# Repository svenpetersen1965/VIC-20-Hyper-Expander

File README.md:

# VIC-20-Hyper-Expander
The Hyper Expander is a cartridge for the Commodore VIC-20, which provides up to 16kB EPROM and up to 37kB RAM. It is a super-set of the original Commodore VIC-1211A Super Expander, which provides only 3k of RAM.

The Hyper Expander can hold up to two 27C512 EPROMs, the 8k memory bank of both EPROMs (A13...A15) can be selected for both EPROMs. The same selection applies to both of them. Each EPROM (IC1 and IC2) can be jumpered to two chip selects. That is BLK2 or BLK5 for IC1 and BLK1 or BLK3 for IC2. 

The RAM od two 32kB 62256 type static RAMs. The memory is divided into seven banks. Two 74LS148s decodes the active chip selects to one of each memory bank. The used chip selects can be configured with JP5 and JP4.

The BOM values do not include a case
* The calculated BOM value of Rev. 0 is: 12.86€ (12.12.2020)
* The calculated BOM value of Rev. 1 is: 15.23€ (11.04.2021)
* The calculated BOM value of Rev. 2 is: 16.17€ (02.11.2021)

# RAM issues
I was recently reported (May 2022), that there were cross-link issues with the Alliance 45ns and 55ns RAMs. I believe, that those might be too fast and that it is not an issue of the brand. Replacing those RAMs with slower models (70ns) has solved this problem. A friend has successfully used 100ns and 120ns RAMs as well (he had built a couple of the Hyper Expander). I am mainly using 70ns and 80ns RAMs and never found any issues with them. At least, my test software can recognize those problems.

# Testsoftware
Find the Testsoftware here: https://github.com/svenpetersen1965/VIC-20-RAM-Expansion-Test-Software

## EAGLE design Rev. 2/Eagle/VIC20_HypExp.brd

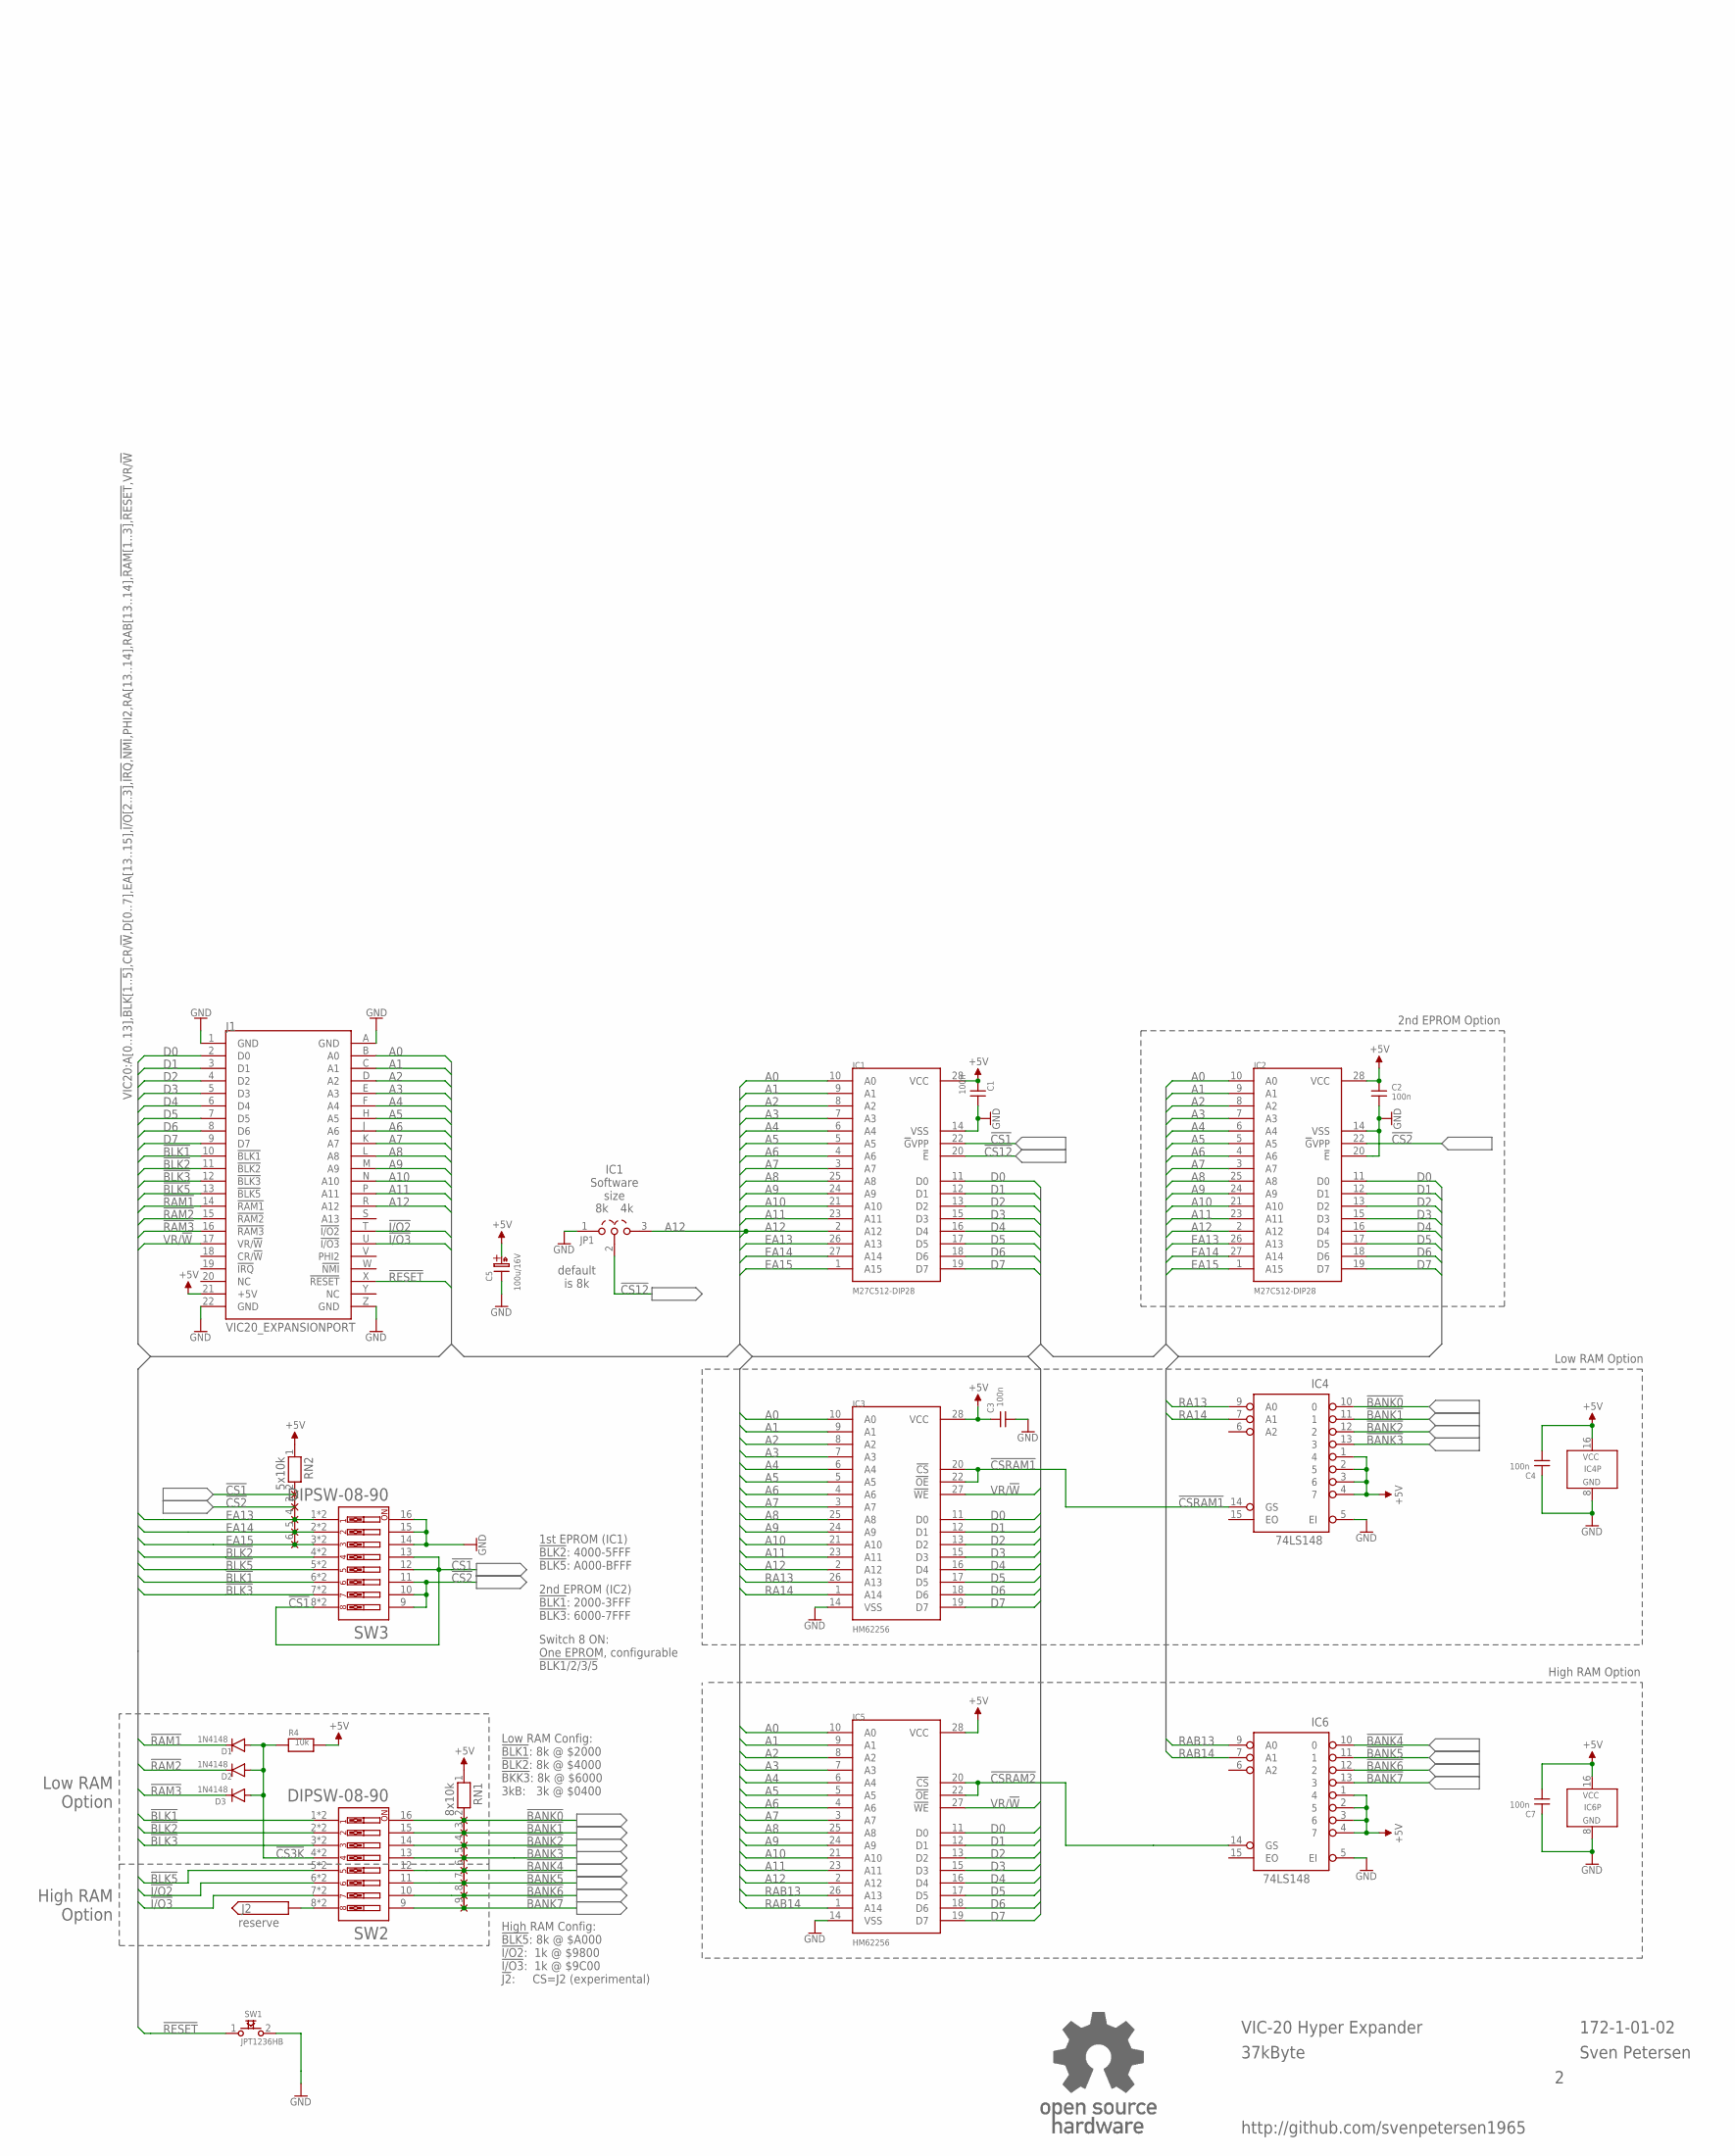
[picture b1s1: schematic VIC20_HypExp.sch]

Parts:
C1, C2, C3, C4, C7: 100n; C-2,5
C5: 100u/16V; C07/2,5
D1, D2, D3: 1N4148; DO-35/3
IC1, IC2: M27C512-DIP28; DIL28-6
IC3, IC5: HM62256; DIL28-6
IC4, IC6: 74LS148; DIL-16
J1: VIC20_EXPANSIONPORT; VIC20_EXPANSION
J2: PINHD-1X1; 1X01
JP1: COMBI-3P
R4: 10k; R-10
RN1: 8x10k; RN-9
RN2: 5x10k; RN-6
SW1: JPT1236HB; JTP_1236HB
SW2, SW3: DIPSW-08-90
U$2: OPEN_SOURCE_HW; OPENHW

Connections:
!BANK0: IC4.10 (0), RN1.2, SW2.16
!BANK1: IC4.11 (1), RN1.3, SW2.15
!BANK2: IC4.12 (2), RN1.4, SW2.14
!BANK3: IC4.13 (3), RN1.5, SW2.13
!BANK4: IC6.10 (0), RN1.6, SW2.12
!BANK5: IC6.11 (1), RN1.7, SW2.11
!BANK6: IC6.12 (2), RN1.8, SW2.10
!BANK7: IC6.13 (3), RN1.9, SW2.9
!BLK1: J1.10 (!BLK1), SW2.1, SW2.1A (1), SW3.6, SW3.6A (6)
!BLK2: J1.11 (!BLK2), SW2.2, SW2.2A (2), SW3.4, SW3.4A (4)
!BLK3: J1.12 (!BLK3), SW2.3, SW2.3A (3), SW3.7, SW3.7A (7)
!BLK5: J1.13 (!BLK5), SW2.5, SW2.5A (5), SW3.5, SW3.5A (5)
!CS1: IC1.22 (!G!VPP), RN2.2, SW3.8, SW3.8A (8), SW3.12, SW3.13
!CS2: IC2.22 (!G!VPP), RN2.3, SW3.9, SW3.10, SW3.11
!CS3K: D1.A, D2.A, D3.A, R4.1, SW2.4, SW2.4A (4)
!CS12: IC1.20 (!E), JP1.2
!CSRAM1: IC3.20 (!CS), IC3.22 (!OE), IC4.14 (GS)
!CSRAM2: IC5.20 (!CS), IC5.22 (!OE), IC6.14 (GS)
!I/O2: J1.T (!I/O2), SW2.6, SW2.6A (6)
!I/O3: J1.U (!I/O3), SW2.7, SW2.7A (7)
!RAM1: D1.K, J1.14 (!RAM1)
!RAM2: D2.K, J1.15 (!RAM2)
!RAM3: D3.K, J1.16 (!RAM3)
!RESET: J1.X (!RESET), SW1.1
+5V: C1.1, C2.1, C3.2, C4.1, C5.A (+), C7.1, IC1.28 (VCC), IC2.28 (VCC), IC3.28 (VCC), IC4.1 (4), IC4.2 (5), IC4.3 (6), IC4.4 (7), IC4.16 (VCC), IC5.28 (VCC), IC6.1 (4), IC6.2 (5), IC6.3 (6), IC6.4 (7), IC6.16 (VCC), J1.21 (+5V), R4.2, RN1.1, RN2.1
A0: IC1.10 (A0), IC2.10 (A0), IC3.10 (A0), IC5.10 (A0), J1.B (A0)
A1: IC1.9 (A1), IC2.9 (A1), IC3.9 (A1), IC5.9 (A1), J1.C (A1)
A2: IC1.8 (A2), IC2.8 (A2), IC3.8 (A2), IC5.8 (A2), J1.D (A2)
A3: IC1.7 (A3), IC2.7 (A3), IC3.7 (A3), IC5.7 (A3), J1.E (A3)
A4: IC1.6 (A4), IC2.6 (A4), IC3.6 (A4), IC5.6 (A4), J1.F (A4)
A5: IC1.5 (A5), IC2.5 (A5), IC3.5 (A5), IC5.5 (A5), J1.H (A5)
A6: IC1.4 (A6), IC2.4 (A6), IC3.4 (A6), IC5.4 (A6), J1.J (A6)
A7: IC1.3 (A7), IC2.3 (A7), IC3.3 (A7), IC5.3 (A7), J1.K (A7)
A8: IC1.25 (A8), IC2.25 (A8), IC3.25 (A8), IC5.25 (A8), J1.L (A8)
A9: IC1.24 (A9), IC2.24 (A9), IC3.24 (A9), IC5.24 (A9), J1.M (A9)
A10: IC1.21 (A10), IC2.21 (A10), IC3.21 (A10), IC5.21 (A10), J1.N (A10)
A11: IC1.23 (A11), IC2.23 (A11), IC3.23 (A11), IC5.23 (A11), J1.P (A11)
A12: IC1.2 (A12), IC2.2 (A12), IC3.2 (A12), IC5.2 (A12), J1.R (A12), JP1.3
D0: IC1.11 (D0), IC2.11 (D0), IC3.11 (D0), IC5.11 (D0), J1.2 (D0)
D1: IC1.12 (D1), IC2.12 (D1), IC3.12 (D1), IC5.12 (D1), J1.3 (D1)
D2: IC1.13 (D2), IC2.13 (D2), IC3.13 (D2), IC5.13 (D2), J1.4 (D2)
D3: IC1.15 (D3), IC2.15 (D3), IC3.15 (D3), IC5.15 (D3), J1.5 (D3)
D4: IC1.16 (D4), IC2.16 (D4), IC3.16 (D4), IC5.16 (D4), J1.6 (D4)
D5: IC1.17 (D5), IC2.17 (D5), IC3.17 (D5), IC5.17 (D5), J1.7 (D5)
D6: IC1.18 (D6), IC2.18 (D6), IC3.18 (D6), IC5.18 (D6), J1.8 (D6)
D7: IC1.19 (D7), IC2.19 (D7), IC3.19 (D7), IC5.19 (D7), J1.9 (D7)
EA13: IC1.26 (A13), IC2.26 (A13), RN2.4, SW3.1, SW3.1A (1)
EA14: IC1.27 (A14), IC2.27 (A14), RN2.5, SW3.2, SW3.2A (2)
EA15: IC1.1 (A15), IC2.1 (A15), RN2.6, SW3.3, SW3.3A (3)
GND: C1.2, C2.2, C3.1, C4.2, C5.K (-), C7.2, IC1.14 (VSS), IC2.14 (VSS), IC2.20 (!E), IC3.14 (VSS), IC4.5 (EI), IC4.8 (GND), IC5.14 (VSS), IC6.5 (EI), IC6.8 (GND), J1.1 (GND), J1.22 (GND), J1.A (GND), J1.Z (GND), JP1.1, SW1.2, SW3.14, SW3.15, SW3.16
unnamed: J2.1, SW2.8, SW2.8A (8)
NC: J1.20 (NC)
RA13: IC3.26 (A13), IC4.9 (A0)
RA14: IC3.1 (A14), IC4.7 (A1)
RAB13: IC5.26 (A13), IC6.9 (A0)
RAB14: IC5.1 (A14), IC6.7 (A1)
VR/!W: IC3.27 (!WE), IC5.27 (!WE), J1.17 (VR/!W)

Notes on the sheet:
VIC-20 Hyper Expander
172-1-01-02
Sven Petersen
http://github.com/svenpetersen1965
reserve
37kByte
High RAM Option
Low RAM Option
Low RAM Option
2nd EPROM Option
1st EPROM (IC1) !BLK2!: 4000-5FFF !BLK5!: A000-BFFF
2nd EPROM (IC2) !BLK1!: 2000-3FFF !BLK3!: 6000-7FFF
Low RAM Config: !BLK1!: 8k @ $2000 !BLK2!: 8k @ $4000 !BKK3!: 8k @ $6000 3kB: 3k @ $0400
High RAM Config: !BLK5!: 8k @ $A000 !I/O2!: 1k @ $9800 !I/O3!: 1k @ $9C00 !J2!: CS=J2 (experimental)
Switch 8 ON: One EPROM, configurable !BLK1/2/3/5
IC1 Software size
default is 8k
High RAM Option

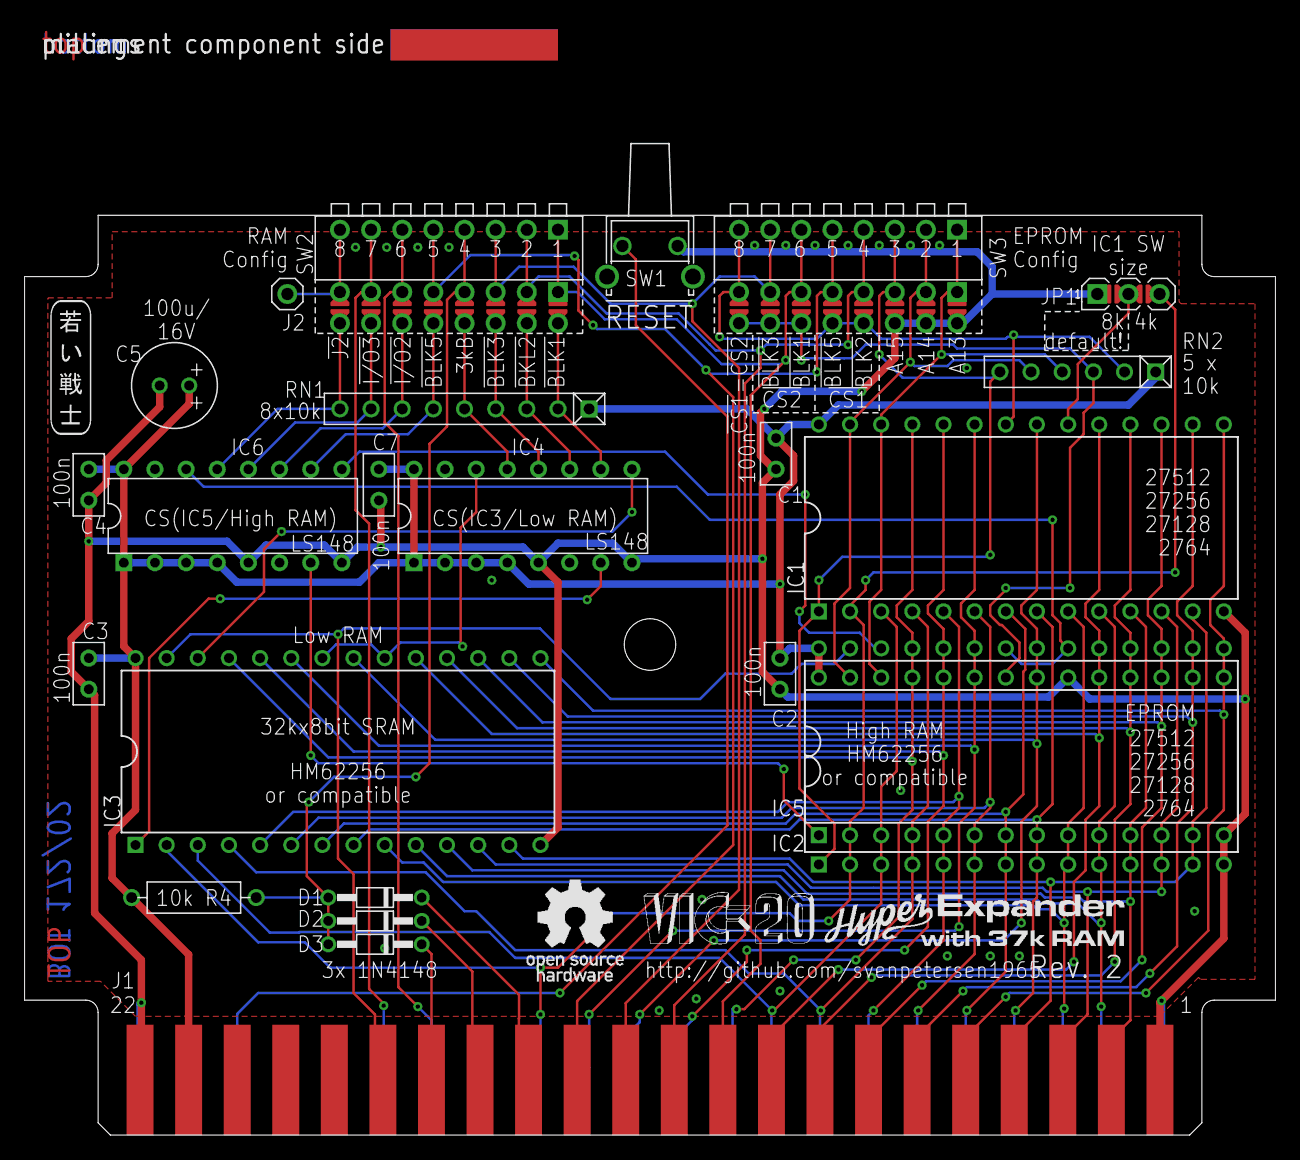
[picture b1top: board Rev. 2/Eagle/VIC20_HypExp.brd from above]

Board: 2 copper layers, 102.0 x 90.6 mm, 30 parts (0 on the bottom side), 56 nets.

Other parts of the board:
U$15: SVEN_TAG
U$16: 2LAYER
U$40: PCB-TITLE/
U$42: VIC-20
U$58: HYPER_EXPANDER

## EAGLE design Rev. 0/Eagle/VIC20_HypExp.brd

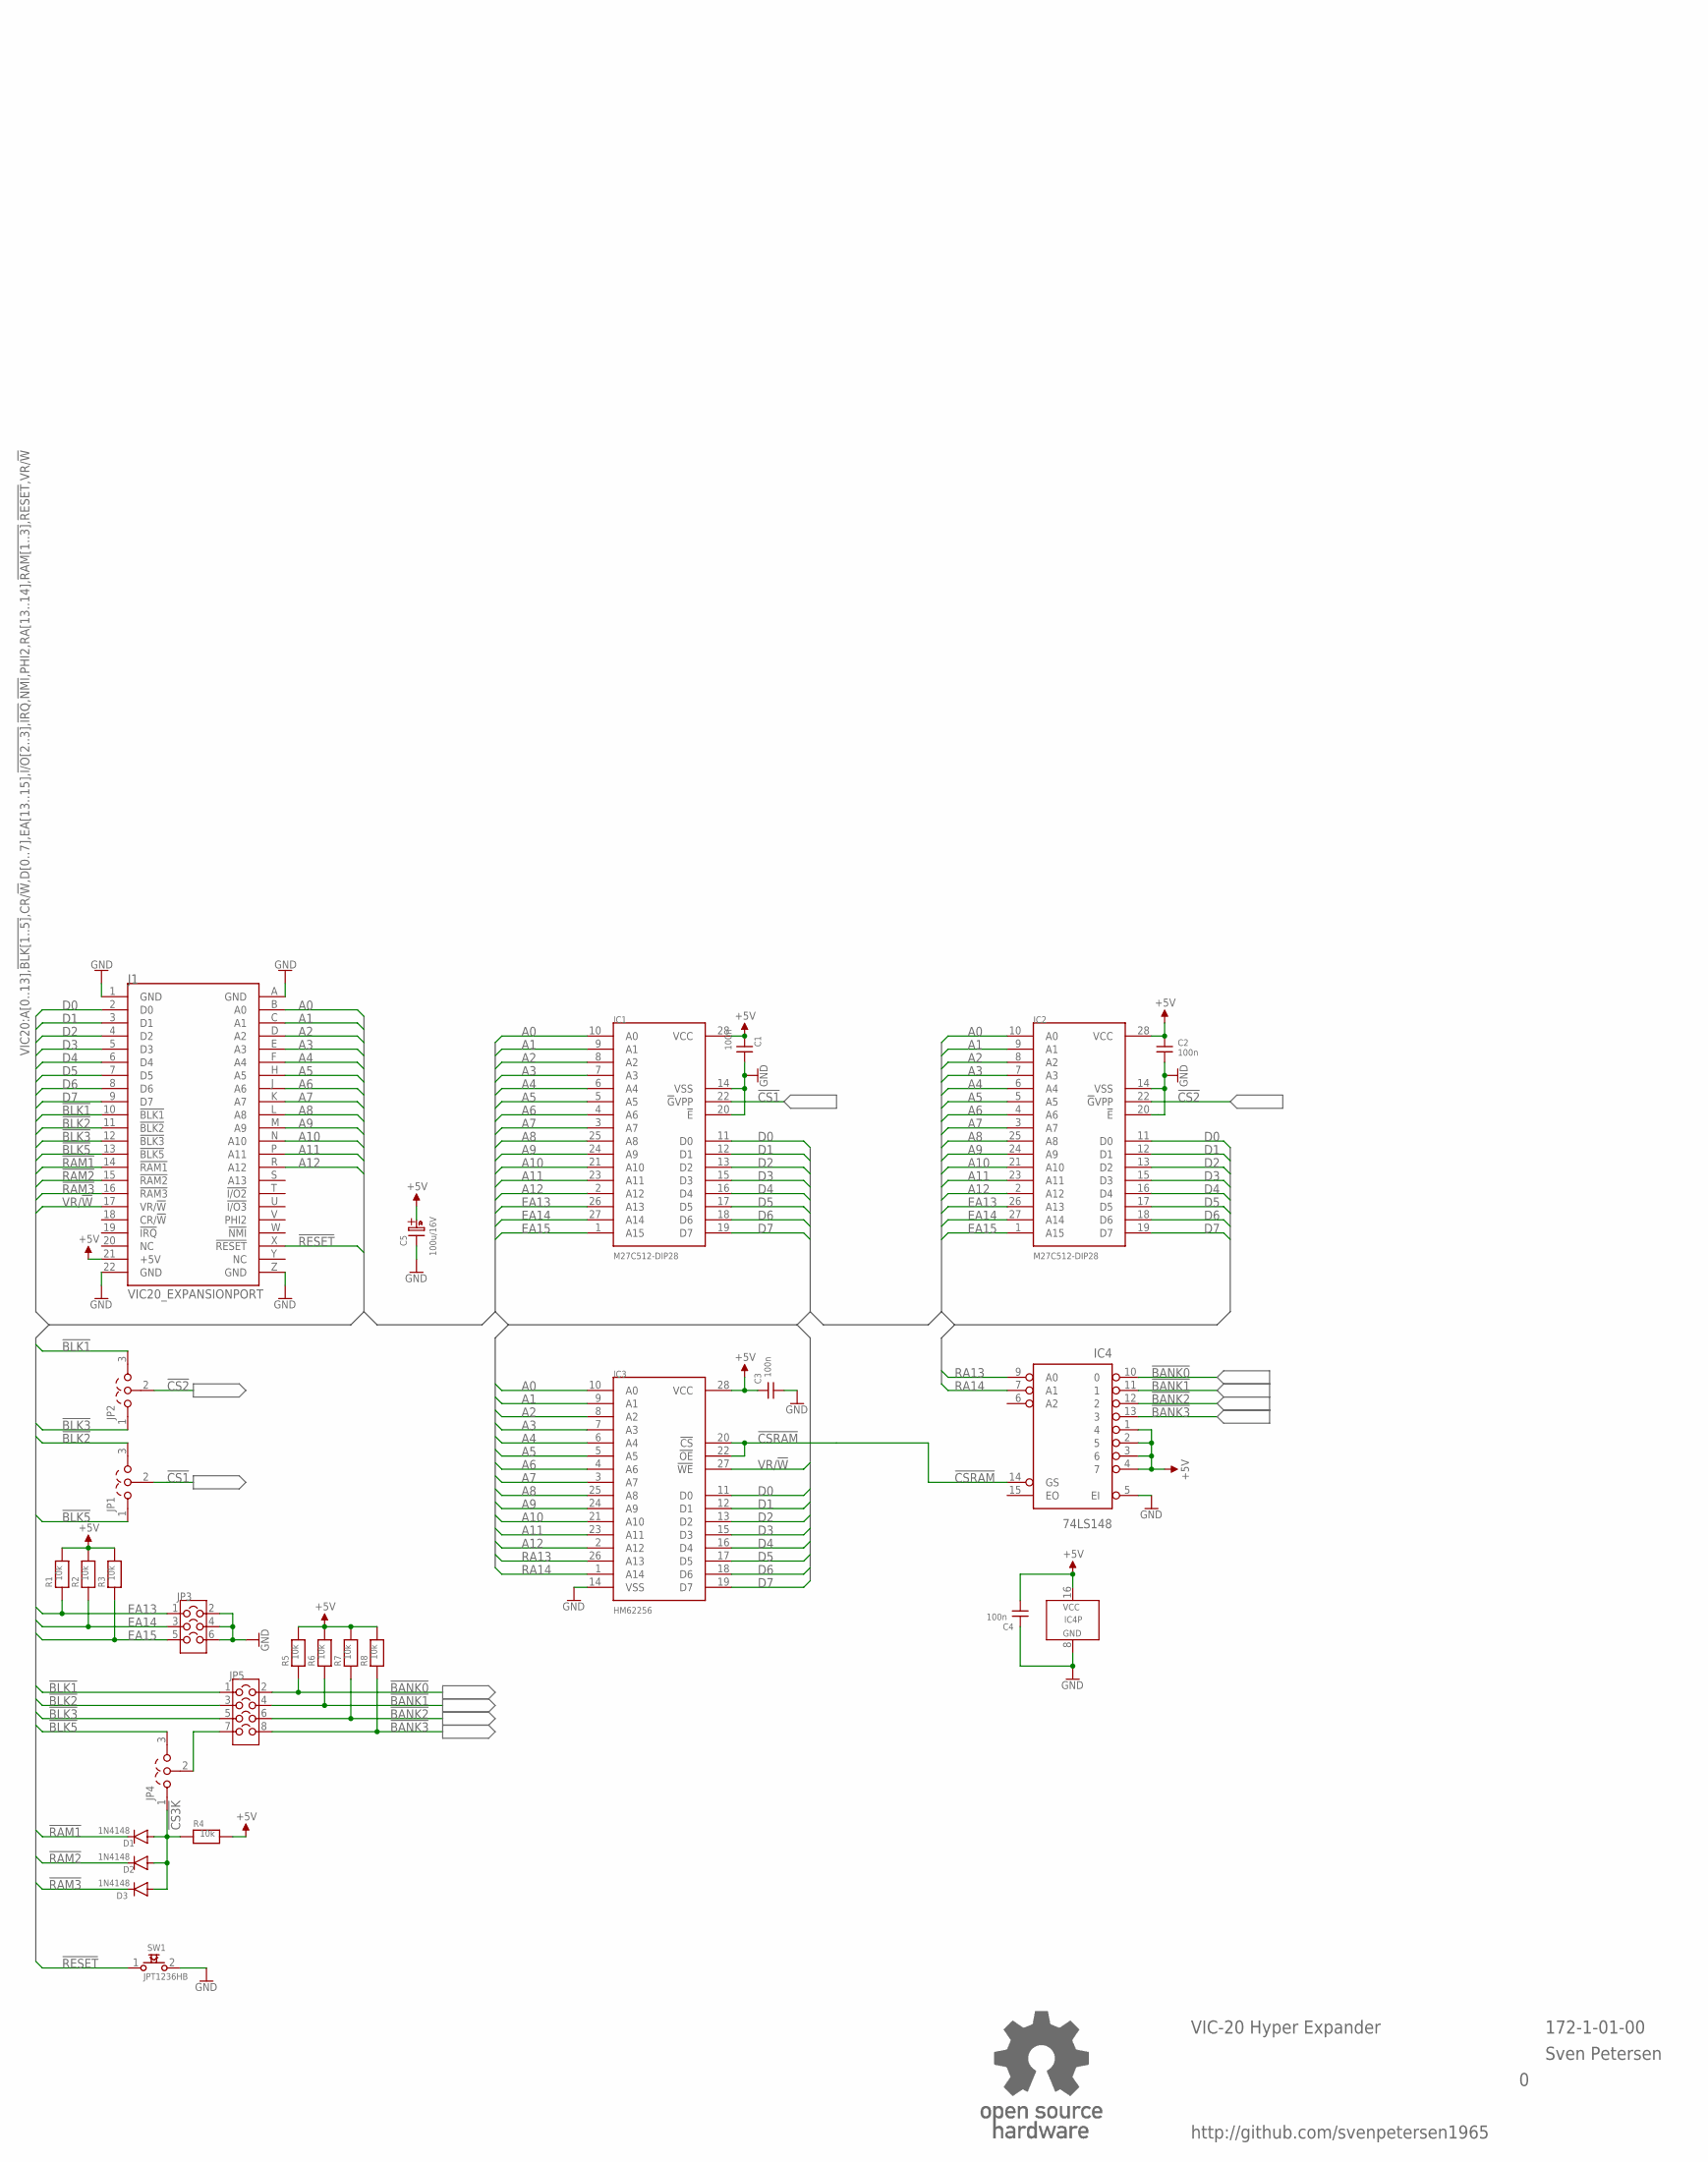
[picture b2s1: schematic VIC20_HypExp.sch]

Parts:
C1, C2, C3, C4: 100n; C-2,5
C5: 100u/16V; C07/2,5
D1, D2, D3: 1N4148; DO-35/3
IC1, IC2: M27C512-DIP28; DIL28-6
IC3: HM62256; DIL28-6
IC4: 74LS148; DIL-16
J1: VIC20_EXPANSIONPORT; VIC20_EXPANSION
JP1, JP2, JP4: COMBI-3P
JP3: COMBI-3X2P; COMBI-3X2
JP5: COMBI-4X2P; COMBI-4X2
R1, R2, R3, R4, R5, R6, R7, R8: 10k; R-10
SW1: JPT1236HB; JTP_1236HB
U$2: OPEN_SOURCE_HW; OPENHW

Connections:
!BANK0: IC4.10 (0), JP5.2, R5.1
!BANK1: IC4.11 (1), JP5.4, R6.1
!BANK2: IC4.12 (2), JP5.6, R7.1
!BANK3: IC4.13 (3), JP5.8, R8.1
!BLK1: J1.10 (!BLK1), JP2.3, JP5.1
!BLK2: J1.11 (!BLK2), JP1.3, JP5.3
!BLK3: J1.12 (!BLK3), JP2.1, JP5.5
!BLK5: J1.13 (!BLK5), JP1.1, JP4.3
!CS1: IC1.22 (!G!VPP), JP1.2
!CS2: IC2.22 (!G!VPP), JP2.2
!CS3K: D1.A, D2.A, D3.A, JP4.1, R4.1
!CSRAM: IC3.20 (!CS), IC3.22 (!OE), IC4.14 (GS)
!RAM1: D1.K, J1.14 (!RAM1)
!RAM2: D2.K, J1.15 (!RAM2)
!RAM3: D3.K, J1.16 (!RAM3)
!RESET: J1.X (!RESET), SW1.1
+5V: C1.1, C2.1, C3.2, C4.1, C5.A (+), IC1.28 (VCC), IC2.28 (VCC), IC3.28 (VCC), IC4.1 (4), IC4.2 (5), IC4.3 (6), IC4.4 (7), IC4.16 (VCC), J1.21 (+5V), R1.2, R2.2, R3.2, R4.2, R5.2, R6.2, R7.2, R8.2
A0: IC1.10 (A0), IC2.10 (A0), IC3.10 (A0), J1.B (A0)
A1: IC1.9 (A1), IC2.9 (A1), IC3.9 (A1), J1.C (A1)
A2: IC1.8 (A2), IC2.8 (A2), IC3.8 (A2), J1.D (A2)
A3: IC1.7 (A3), IC2.7 (A3), IC3.7 (A3), J1.E (A3)
A4: IC1.6 (A4), IC2.6 (A4), IC3.6 (A4), J1.F (A4)
A5: IC1.5 (A5), IC2.5 (A5), IC3.5 (A5), J1.H (A5)
A6: IC1.4 (A6), IC2.4 (A6), IC3.4 (A6), J1.J (A6)
A7: IC1.3 (A7), IC2.3 (A7), IC3.3 (A7), J1.K (A7)
A8: IC1.25 (A8), IC2.25 (A8), IC3.25 (A8), J1.L (A8)
A9: IC1.24 (A9), IC2.24 (A9), IC3.24 (A9), J1.M (A9)
A10: IC1.21 (A10), IC2.21 (A10), IC3.21 (A10), J1.N (A10)
A11: IC1.23 (A11), IC2.23 (A11), IC3.23 (A11), J1.P (A11)
A12: IC1.2 (A12), IC2.2 (A12), IC3.2 (A12), J1.R (A12)
D0: IC1.11 (D0), IC2.11 (D0), IC3.11 (D0), J1.2 (D0)
D1: IC1.12 (D1), IC2.12 (D1), IC3.12 (D1), J1.3 (D1)
D2: IC1.13 (D2), IC2.13 (D2), IC3.13 (D2), J1.4 (D2)
D3: IC1.15 (D3), IC2.15 (D3), IC3.15 (D3), J1.5 (D3)
D4: IC1.16 (D4), IC2.16 (D4), IC3.16 (D4), J1.6 (D4)
D5: IC1.17 (D5), IC2.17 (D5), IC3.17 (D5), J1.7 (D5)
D6: IC1.18 (D6), IC2.18 (D6), IC3.18 (D6), J1.8 (D6)
D7: IC1.19 (D7), IC2.19 (D7), IC3.19 (D7), J1.9 (D7)
EA13: IC1.26 (A13), IC2.26 (A13), JP3.1, R1.1
EA14: IC1.27 (A14), IC2.27 (A14), JP3.3, R2.1
EA15: IC1.1 (A15), IC2.1 (A15), JP3.5, R3.1
GND: C1.2, C2.2, C3.1, C4.2, C5.K (-), IC1.14 (VSS), IC1.20 (!E), IC2.14 (VSS), IC2.20 (!E), IC3.14 (VSS), IC4.5 (EI), IC4.8 (GND), J1.1 (GND), J1.22 (GND), J1.A (GND), J1.Z (GND), JP3.2, JP3.4, JP3.6, SW1.2
unnamed: JP4.2, JP5.7
NC: J1.20 (NC)
RA13: IC3.26 (A13), IC4.9 (A0)
RA14: IC3.1 (A14), IC4.7 (A1)
VR/!W: IC3.27 (!WE), J1.17 (VR/!W)

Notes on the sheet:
VIC-20 Hyper Expander
172-1-01-00
Sven Petersen
http://github.com/svenpetersen1965

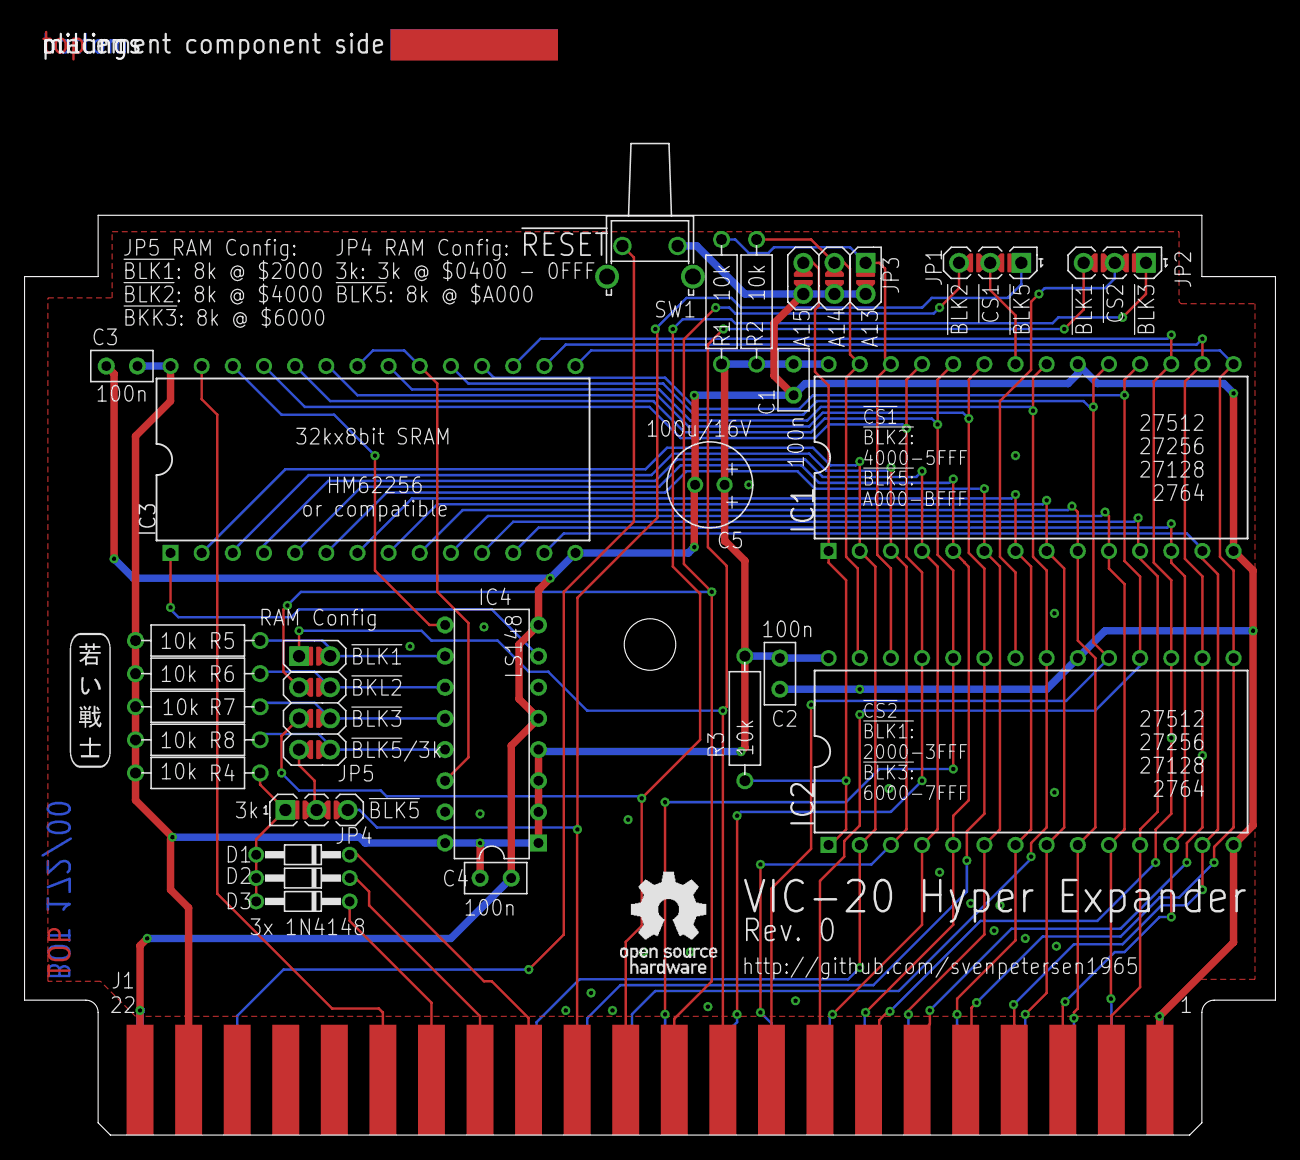
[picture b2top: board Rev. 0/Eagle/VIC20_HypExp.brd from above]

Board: 2 copper layers, 102.0 x 90.6 mm, 31 parts (0 on the bottom side), 46 nets.

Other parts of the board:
U$15: SVEN_TAG
U$16: 2LAYER
U$40: PCB-TITLE/

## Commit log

2020-12-12 Added calculation
2021-05-05 Updated to RAM-Test Rev. 1
2021-05-05 Rev. 1 released
2021-06-03 Labels added
2021-11-02 Rev. 2 released
2022-02-26 Gerbers removed
2022-05-27 Add files via upload
    Alliance 45ns RAM
